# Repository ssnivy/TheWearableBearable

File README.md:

## Introduction

The Wearable Bearable is a prototype wearable haptic timing system that helps groups stay synchronized through shared vibration cues. It was originally developed for the **Interplay Orchestra**, a nonprofit ensemble for adults with disabilities, where some musicians may benefit from an additional tactile signal to reinforce the conductor’s tempo.

The system consists of one master device and one or more slave devices. A phone or other Bluetooth Low Energy (BLE) controller sends a selected tempo in beats per minute (BPM) to the master. The master converts that tempo into timed vibration pulses, activates its own motor, and broadcasts synchronization commands to nearby slaves using ESP-NOW. Each slave reproduces the same short vibration pulses, allowing all connected wearers to receive a coordinated tactile beat without physical connections between devices.

The project explores low-cost wearable haptic feedback as an accessibility tool for shared timing and coordination. The Wearable Bearable is a prototype and is not a medical device; it does not measure heart rate or diagnose, monitor, or treat any medical condition.

## Hardware

The custom KiCad PCB is built around the **Seeed Studio XIAO ESP32-C6** and includes:
- Vibration motor connection and MOSFET driver
- Flyback diode for motor protection
- WS2812B-2020 RGB LED
- Push button
- Supporting resistors and capacitors

The vibration motor is controlled through the MOSFET rather than directly from a GPIO pin, while the flyback diode protects the circuit from voltage spikes produced by the motor.

The PCB schematic, layout, component footprints, 3D models, and design backups are located in `KiCAD PCB/`.

## Enclosure

The electronics are housed inside a custom 3D-printed bear-shaped enclosure mounted to an adjustable wristband. The enclosure is designed to securely hold the PCB while allowing the vibration to be felt through the wrist or forearm.

The enclosure was designed in Onshape.

**Onshape Model:** [View CAD Design](https://cad.onshape.com/documents/7e5ceedf84fb8e6fbe93ee03/w/6ff0015e9bba8e7b5cdaebe4/e/c4b1ddca45680bea3a319f90?renderMode=0&uiState=6a83e70f9db896020d9f8f01)

## Firmware

The Arduino sketches are located in `ESP32c6 Code/`:
- `MasterCode.ino` receives a BPM value over BLE, controls the local vibration motor, and broadcasts the BPM using ESP-NOW.
- `SlaveCode.ino` receives the ESP-NOW command and reproduces the vibration rhythm.

A BPM value of `0` stops the rhythm. Values above `200` BPM are limited to `200`.

The planned communication system also includes support for device/group IDs, relay networking, and synchronization compensation so larger groups can remain coordinated even when some devices are outside the master’s direct range.

## Software (App)

Special thanks to Katherine Xu for designing the app.

The **Bearable** ao is the control application for the Wearable Bearable system. It allows the conductor to connect to the master device over BLE, set the desired tempo, and start or stop the synchronized haptic rhythm.

The application is currently built for Android and works alongside the ESP32-C6 firmware in this repository. Future software development may include group management, saved songs/tempos, improved pairing, and additional calibration controls.

**Bearable App Repository:**  [View Repository](https://github.com/kaatxu/Bearable)

Download the APK [here](https://drive.google.com/file/d/1Ic-rRA5f5QP9VBr-pHBqYD8MdoO2g-DN/view) and install like a normal app.

## Project Status

Wearable Bearable is currently an engineering prototype. The repository contains the PCB design, proof-of-concept firmware, Android control application, and 3D-printed wearable enclosure.

Planned features include expanded group management, relay networking, synchronization calibration, LED status indicators, and a more finalized communication protocol.

## Credits

Wearable Bearable was created by **Akash Saran**, **Katherine Xu**, and **Anna Zhou**.

Credit to my best friend **Katherine Xu** for designing the **Bearable** React app (currently on Android) that controls the device and **Anna Zhou** for maintaining all communication efforts with Wearable's sponsors.

Special thanks to the **Interplay Orchestra** and Technical Director **Shri Khalpada** for supporting the project and providing feedback throughout development.

The repository includes component symbols, footprints, reference designs, and supporting assets from the **Seeed Studio Open Parts Library and Seeed Studio XIAO ecosystem**. Those third-party materials remain subject to their respective licenses and attribution requirements.

## Status

Project Originally Started: **10/17/2025**  
Github Saved: **8/18/2026**

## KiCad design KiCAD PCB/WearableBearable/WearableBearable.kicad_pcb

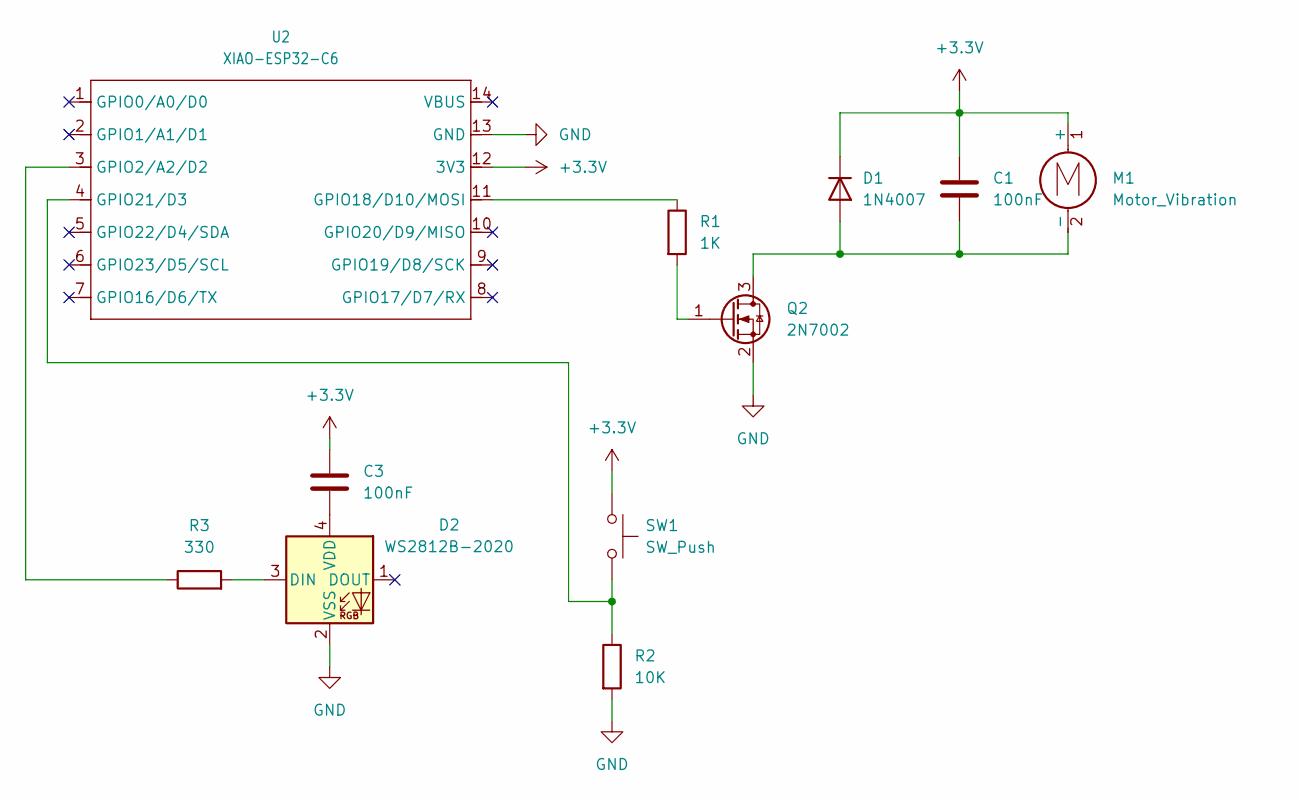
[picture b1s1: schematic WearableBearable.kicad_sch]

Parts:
C1, C3: 100nF; C_Disc_D4.7mm_W2.5mm_P5.00mm
D1: 1N4007; D_DO-41_SOD81_P10.16mm_Horizontal
D2: WS2812B-2020; LED_WS2812B-2020_PLCC4_2.0x2.0mm
M1: Motor_Vibration; TerminalBlock_Phoenix_MKDS-1,5-2_1x02_P5.00mm_Horizontal
Q2: 2N7002; SOT-23
R1: 1K; R_Axial_DIN0207_L6.3mm_D2.5mm_P7.62mm_Horizontal
R2: 10K; R_Axial_DIN0207_L6.3mm_D2.5mm_P7.62mm_Horizontal
R3: 330; R_Axial_DIN0207_L6.3mm_D2.5mm_P7.62mm_Horizontal
SW1: SW_Push; SW_PUSH_6mm
U2: XIAO-ESP32-C6; XIAO-ESP32C6-DIP

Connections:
+3.3V: C1.1, C3.1, D1.1 (K), M1.1 (+), SW1.1, U2.12 (3V3)
GND: D2.2 (VSS), Q2.2 (S), R2.2, U2.13 (GND)
unnamed: C1.2, D1.2 (A), M1.2 (-), Q2.3 (D)
unnamed: D2.3 (DIN), R3.2
unnamed: C3.2, D2.4 (VDD)
unnamed: Q2.1 (G), R1.2
unnamed: R3.1, U2.3 (GPIO2/A2/D2)
unnamed: R1.1, U2.11 (GPIO18/D10/MOSI)
unnamed: R2.1, SW1.2, U2.4 (GPIO21/D3)

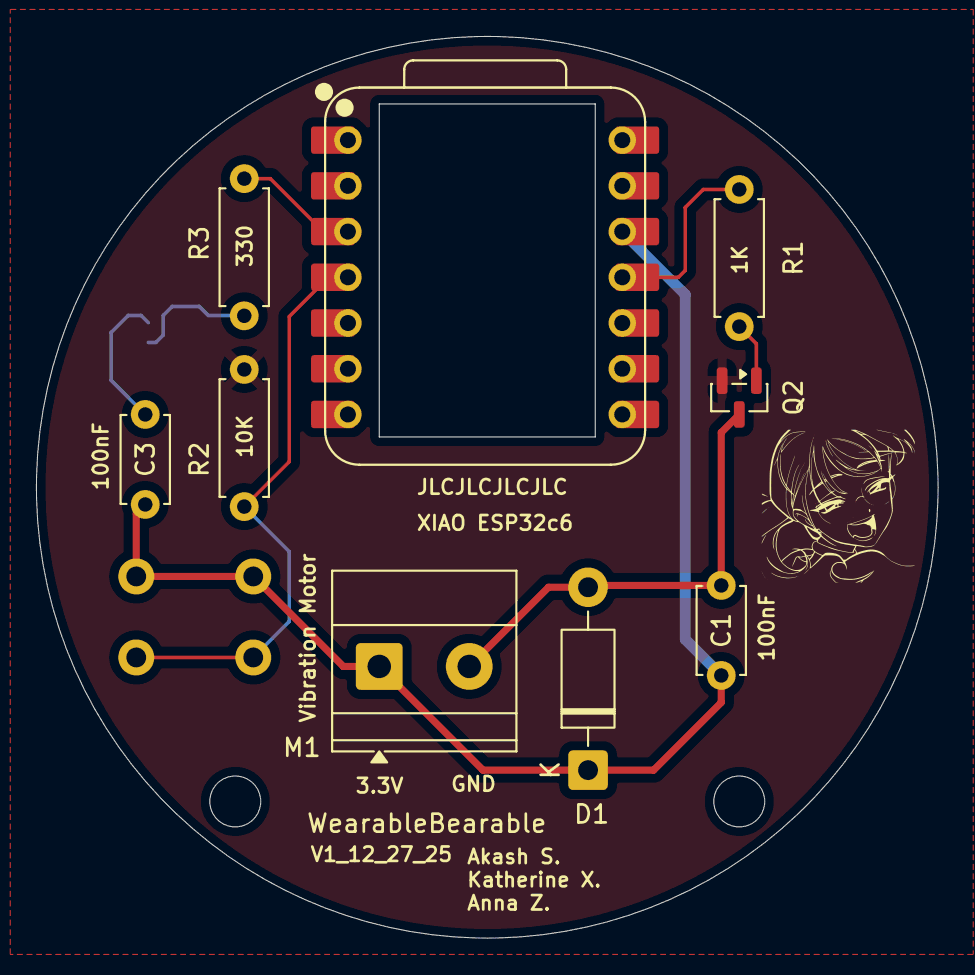
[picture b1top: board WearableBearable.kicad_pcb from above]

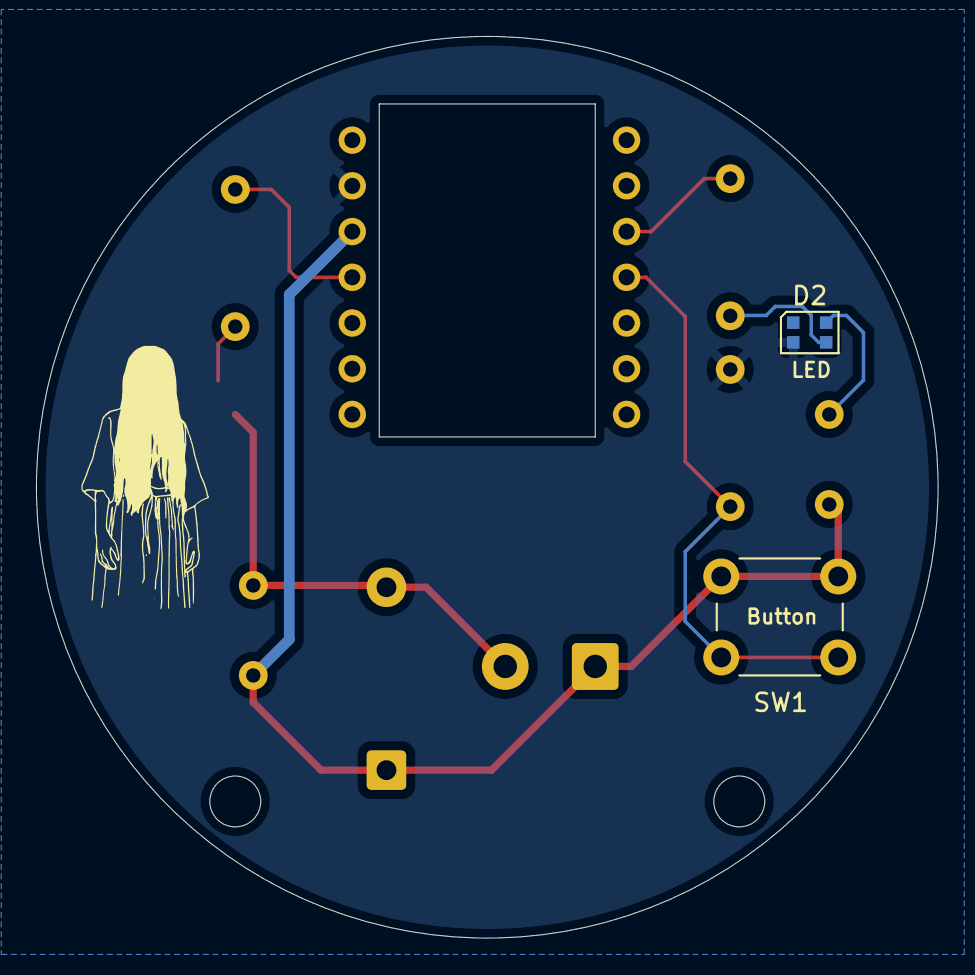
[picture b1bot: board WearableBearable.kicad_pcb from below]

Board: 4 copper layers, 50.1 x 50.1 mm, 11 parts (2 on the bottom side), 9 nets.
